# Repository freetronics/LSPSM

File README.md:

Freetronics LibreSat Power Supply Module
========================================
Copyright 2013 Freetronics Pty Ltd  
Freetronics site:  www.freetronics.com.au  
Freetronics email: info@freetronics.com.au  

FIXME

Features:

 * FIXME

More information is available at:

  http://www.freetronics.com.au/lspsm

INSTALLATION
------------
The design is saved as an EAGLE project. EAGLE PCB design software is
available from www.cadsoftusa.com free for non-commercial use. To use
this project download it and place the directory containing these files
into the "eagle" directory on your computer. Then open EAGLE and
navigate to the project.

DISTRIBUTION
------------
The specific terms of distribution of this project are governed by the
license referenced below.

LICENSE
-------
Licensed under the TAPR Open Hardware License (www.tapr.org/OHL).
The "license" folder within this repository also contains a copy of
this license in plain text format.

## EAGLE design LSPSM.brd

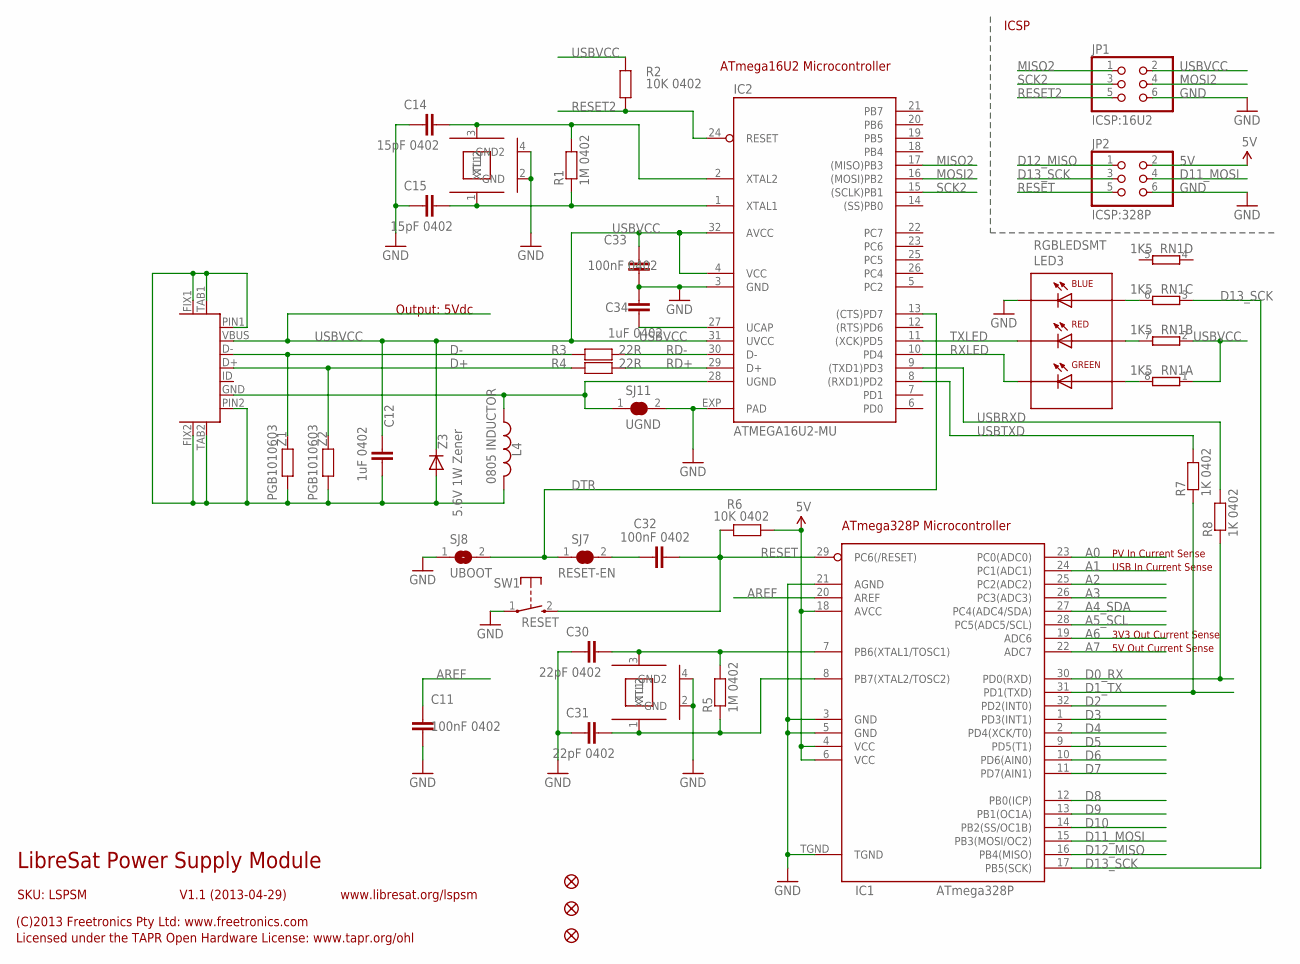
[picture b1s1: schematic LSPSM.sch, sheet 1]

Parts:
C11, C32, C33: 100nF 0402; 0402C
C12, C34: 1uF 0402; 0402C
C14, C15: 15pF 0402; 0402C
C30, C31: 22pF 0402; 0402C
FID1, FID2, FID3: FIDUCIAL1X2.5; FIDUCIAL-1X2.5
IC1: ATmega328P; MLF32
IC2: ATMEGA16U2-MU; ATMEL_QFN32
JP1: ICSP:16U2; 2X03
JP2: ICSP:328P; 2X03
L4: 0805 INDUCTOR; 0805-LARGE
LED3: RGBLEDSMT; 19-337
R1, R5: 1M 0402; 0402
R2, R6: 10K 0402; 0402
R3, R4: 22R; 0402
R7, R8: 1K 0402; 0402
RN1: 1K5; CAY16
S1: USB-6PSMT; USB-MICROB-MB05PMXX
SJ7: RESET-EN; 0402SJC
SJ8: UBOOT; 0402SJO
SJ11: UGND; 0402SJC
SW1: RESET; TACTILE_SWITCH_SMD_2PIN_TINY
XTL1, XTL2: 16MHz; CRYSTAL-SMD-3X2
Z1, Z2: PGB1010603; 0603
Z3: 5.6V 1W Zener; SMA-DIODE

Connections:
5V: IC1.4 (VCC), IC1.6 (VCC), IC1.18 (AVCC), JP2.2, R6.2; also elsewhere on the board
A0: IC1.23 (PC0(ADC0)); also elsewhere on the board
A1: IC1.24 (PC1(ADC1)); also elsewhere on the board
A2: IC1.25 (PC2(ADC2)); also elsewhere on the board
A3: IC1.26 (PC3(ADC3)); also elsewhere on the board
A4_SDA: IC1.27 (PC4(ADC4/SDA)); also elsewhere on the board
A5_SCL: IC1.28 (PC5(ADC5/SCL)); also elsewhere on the board
A6: IC1.19 (ADC6); also elsewhere on the board
A7: IC1.22 (ADC7); also elsewhere on the board
AREF: C11.1, IC1.20 (AREF); also elsewhere on the board
D0_RX: IC1.30 (PD0(RXD)), R8.1; also elsewhere on the board
D1_TX: IC1.31 (PD1(TXD)), R7.1; also elsewhere on the board
D2: IC1.32 (PD2(INT0)); also elsewhere on the board
D3: IC1.1 (PD3(INT1)); also elsewhere on the board
D4: IC1.2 (PD4(XCK/T0)); also elsewhere on the board
D5: IC1.9 (PD5(T1)); also elsewhere on the board
D6: IC1.10 (PD6(AIN0)); also elsewhere on the board
D7: IC1.11 (PD7(AIN1)); also elsewhere on the board
D8: IC1.12 (PB0(ICP)); also elsewhere on the board
D9: IC1.13 (PB1(OC1A)); also elsewhere on the board
D10: IC1.14 (PB2(SS/OC1B)); also elsewhere on the board
D11_MOSI: IC1.15 (PB3(MOSI/OC2)), JP2.4; also elsewhere on the board
D12_MISO: IC1.16 (PB4(MISO)), JP2.1; also elsewhere on the board
D13_SCK: IC1.17 (PB5(SCK)), JP2.3, RN1.3 (1); also elsewhere on the board
D+: R4.1, S1.D+, Z2.2
D-: R3.1, S1.D-, Z1.2
DTR: IC2.13 ((CTS)PD7), SJ7.1, SJ8.2
GND: C11.2, C14.1, C15.1, C30.1, C31.1, C33.2, C34.2, IC1.3 (GND), IC1.5 (GND), IC1.21 (AGND), IC1.TGND, IC2.3 (GND), IC2.EXP (PAD), JP1.6, JP2.6, LED3.1 (C-B), SJ8.1, SJ11.2, SW1.1, XTL1.2 (GND), XTL1.4 (GND2), XTL2.2 (GND), XTL2.4 (GND2); also elsewhere on the board
MISO2: IC2.17 ((MISO)PB3), JP1.1
MOSI2: IC2.16 ((MOSI)PB2), JP1.4
unnamed: C30.2, IC1.7 (PB6(XTAL1/TOSC1)), R5.2, XTL2.3 (XTL2)
unnamed: C15.2, IC2.1 (XTAL1), R1.1, XTL1.1 (XTL1)
unnamed: LED3.4 (A-B), RN1.6 (2)
unnamed: LED3.5 (A-R), RN1.7 (2)
unnamed: LED3.6 (A-G), RN1.8 (2)
unnamed: C31.2, IC1.8 (PB7(XTAL2/TOSC2)), R5.1, XTL2.1 (XTL1)
unnamed: C34.1, IC2.27 (UCAP)
unnamed: C12.2, L4.2, S1.FIX1, S1.FIX2, S1.PIN1, S1.PIN2, S1.TAB1, S1.TAB2, Z1.1, Z2.1, Z3.A
unnamed: C14.2, IC2.2 (XTAL2), R1.2, XTL1.3 (XTL2)
unnamed: IC2.28 (UGND), L4.1, S1.GND, SJ11.1
unnamed: C32.1, SJ7.2
RD+: IC2.29 (D+), R4.2
RD-: IC2.30 (D-), R3.2
RESET: C32.2, IC1.29 (PC6(/RESET)), JP2.5, R6.1, SW1.2 (S); also elsewhere on the board
RESET2: IC2.24 (RESET), JP1.5, R2.1
RXLED: IC2.10 (PD4), LED3.3 (C-G)
SCK2: IC2.15 ((SCLK)PB1), JP1.3
TXLED: IC2.11 ((XCK)PD5), LED3.2 (C-R)
USBRXD: IC2.9 ((TXD1)PD3), R8.2
USBTXD: IC2.8 ((RXD1)PD2), R7.2
USBVCC: C12.1, C33.1, IC2.4 (VCC), IC2.31 (UVCC), IC2.32 (AVCC), JP1.2, R2.2, RN1.1, RN1.2 (1), S1.VBUS, Z3.C; also elsewhere on the board

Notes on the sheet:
ATmega328P Microcontroller
ATmega16U2 Microcontroller
PV In Current Sense
5V Out Current Sense
3V3 Out Current Sense
USB In Current Sense
Output: 5Vdc
LibreSat Power Supply Module
V1.1 (2013-04-29)
SKU: LSPSM
(C)2013 Freetronics Pty Ltd: www.freetronics.com
Licensed under the TAPR Open Hardware License: www.tapr.org/ohl
www.libresat.org/lspsm
ICSP

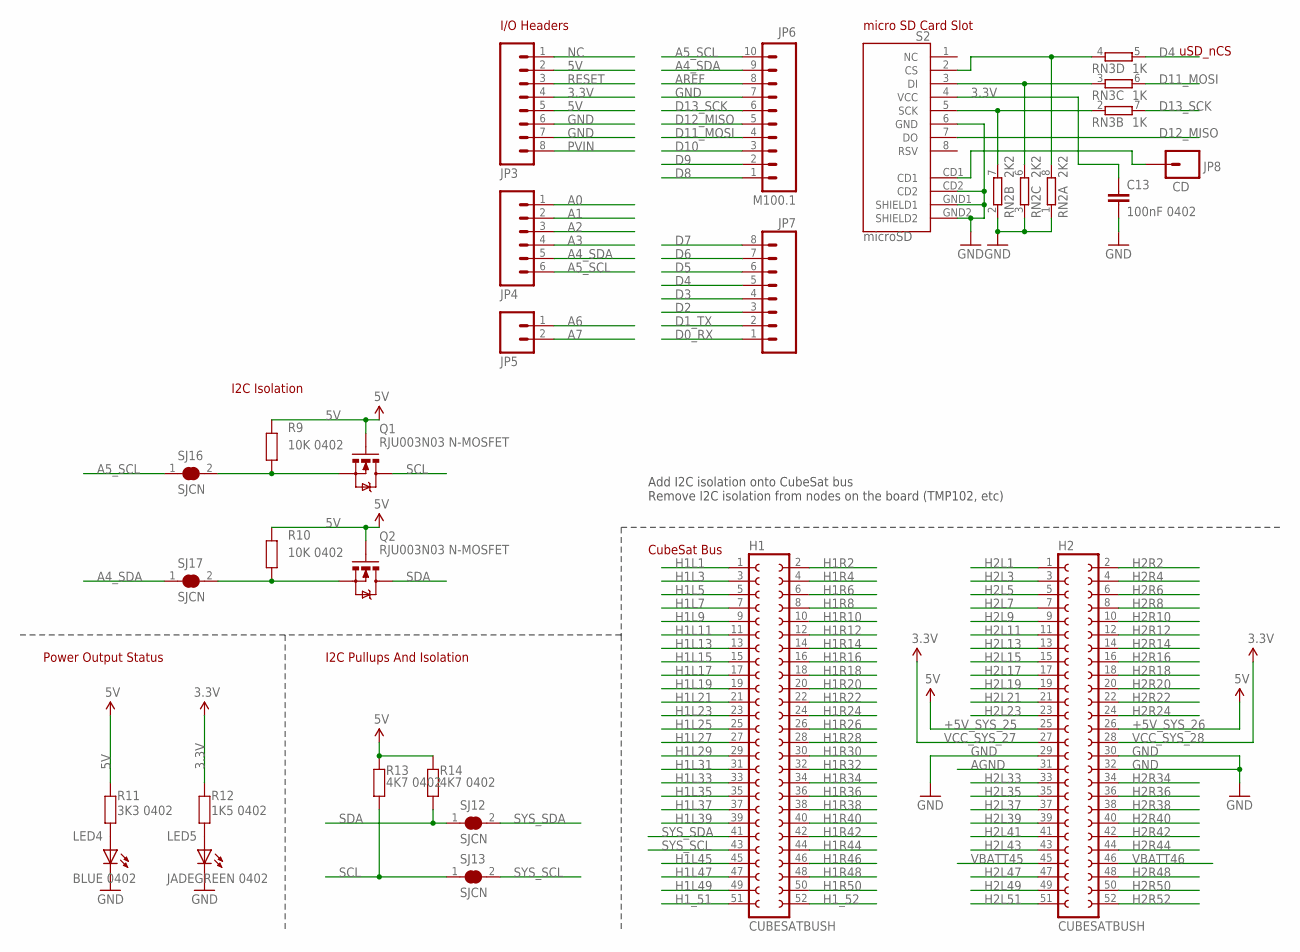
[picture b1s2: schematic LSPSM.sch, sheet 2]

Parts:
C13: 100nF 0402; 0402C
H1, H2: CUBESATBUSH; CUBESATBUS
JP3, JP7: M08; 1X08
JP4: M06SIP; 1X06
JP5: M02PTH; 1X02
JP6: M100.1; 1X10
JP8: CD; 1X01
LED4: BLUE 0402; LED-0402
LED5: JADEGREEN 0402; LED-0402
Q1, Q2: RJU003N03 N-MOSFET; SOT32-3
R9, R10: 10K 0402; 0402
R11: 3K3 0402; 0402
R12: 1K5 0402; 0402
R13, R14: 4K7 0402; 0402
RN2: 2K2; CAY16
RN3: 1K; CAY16
S2: microSD; MICRO-SD-SOCKET-PP
SJ12, SJ13, SJ16, SJ17: SJCN; SJC

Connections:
3.3V: C13.1, JP3.4, R12.1, S2.4 (VCC); also elsewhere on the board
5V: JP3.2, JP3.5, Q1.1 (G), Q2.1 (G), R9.2, R10.2, R11.1, R13.2, R14.2; also elsewhere on the board
+5V_SYS_25: H2.25; also elsewhere on the board
+5V_SYS_26: H2.26; also elsewhere on the board
A0: JP4.1; also elsewhere on the board
A1: JP4.2; also elsewhere on the board
A2: JP4.3; also elsewhere on the board
A3: JP4.4; also elsewhere on the board
A4_SDA: JP4.5, JP6.9, SJ17.1; also elsewhere on the board
A5_SCL: JP4.6, JP6.10, SJ16.1; also elsewhere on the board
A6: JP5.1; also elsewhere on the board
A7: JP5.2; also elsewhere on the board
AGND: H2.31
AREF: JP6.8; also elsewhere on the board
D0_RX: JP7.1; also elsewhere on the board
D1_TX: JP7.2; also elsewhere on the board
D2: JP7.3; also elsewhere on the board
D3: JP7.4; also elsewhere on the board
D4: JP7.5, RN3.5 (2); also elsewhere on the board
D5: JP7.6; also elsewhere on the board
D6: JP7.7; also elsewhere on the board
D7: JP7.8; also elsewhere on the board
D8: JP6.1; also elsewhere on the board
D9: JP6.2; also elsewhere on the board
D10: JP6.3; also elsewhere on the board
D11_MOSI: JP6.4, RN3.6 (2); also elsewhere on the board
D12_MISO: JP6.5, S2.7 (DO); also elsewhere on the board
D13_SCK: JP6.6, RN3.7 (2); also elsewhere on the board
GND: C13.2, H2.29, H2.30, H2.32, JP3.6, JP3.7, JP6.7, LED4.C, LED5.C, RN2.1, RN2.2 (1), RN2.3 (1), S2.6 (GND), S2.CD2, S2.GND1 (SHIELD1), S2.GND2 (SHIELD2); also elsewhere on the board
H1L1: H1.1
H1L3: H1.3
H1L5: H1.5
H1L7: H1.7
H1L9: H1.9
H1L11: H1.11
H1L13: H1.13
H1L15: H1.15
H1L17: H1.17
H1L19: H1.19
H1L21: H1.21
H1L23: H1.23
H1L25: H1.25
H1L27: H1.27
H1L29: H1.29
H1L31: H1.31
H1L33: H1.33
H1L35: H1.35
H1L37: H1.37
H1L39: H1.39
H1L45: H1.45
H1L47: H1.47
H1L49: H1.49
H1R2: H1.2
H1R4: H1.4
H1R6: H1.6
H1R8: H1.8
H1R10: H1.10
H1R12: H1.12
H1R14: H1.14
H1R16: H1.16
H1R18: H1.18
H1R20: H1.20
H1R22: H1.22
H1R24: H1.24
H1R26: H1.26
H1R28: H1.28
H1R30: H1.30
H1R32: H1.32
H1R34: H1.34
H1R36: H1.36
H1R38: H1.38
H1R40: H1.40
H1R42: H1.42
H1R44: H1.44
H1R46: H1.46
H1R48: H1.48
H1R50: H1.50
H1_51: H1.51
H1_52: H1.52
H2L1: H2.1
H2L3: H2.3
H2L5: H2.5
H2L7: H2.7
H2L9: H2.9
H2L11: H2.11
H2L13: H2.13
H2L15: H2.15
H2L17: H2.17
H2L19: H2.19
H2L21: H2.21
H2L23: H2.23
H2L33: H2.33
H2L35: H2.35
H2L37: H2.37
H2L39: H2.39
H2L41: H2.41
H2L43: H2.43
H2L47: H2.47
H2L49: H2.49
H2L51: H2.51
H2R2: H2.2
H2R4: H2.4
H2R6: H2.6
H2R8: H2.8
H2R10: H2.10
H2R12: H2.12
H2R14: H2.14
H2R16: H2.16
H2R18: H2.18
H2R20: H2.20
H2R22: H2.22
H2R24: H2.24
H2R34: H2.34
H2R36: H2.36
H2R38: H2.38
H2R40: H2.40
H2R42: H2.42
H2R44: H2.44
H2R48: H2.48
H2R50: H2.50
H2R52: H2.52
unnamed: LED5.A, R12.2
unnamed: LED4.A, R11.2
unnamed: RN2.8 (2), RN3.4 (1), S2.2 (CS)
unnamed: RN2.6 (2), RN3.3 (1), S2.3 (DI)
unnamed: RN2.7 (2), RN3.2 (1), S2.5 (SCK)
unnamed: JP8.1, S2.CD1
unnamed: Q1.2 (S), R9.1, SJ16.2
unnamed: Q2.2 (S), R10.1, SJ17.2
NC: JP3.1
PVIN: JP3.8; also elsewhere on the board
RESET: JP3.3; also elsewhere on the board
SCL: Q1.3 (D), R13.1, SJ13.1; also elsewhere on the board
SDA: Q2.3 (D), R14.1, SJ12.1; also elsewhere on the board
SYS_SCL: H1.43, SJ13.2
SYS_SDA: H1.41, SJ12.2
VBATT45: H2.45; also elsewhere on the board
VBATT46: H2.46; also elsewhere on the board
VCC_SYS_27: H2.27; also elsewhere on the board
VCC_SYS_28: H2.28; also elsewhere on the board

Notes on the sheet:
CubeSat Bus
Power Output Status
I2C Pullups And Isolation
uSD_nCS
micro SD Card Slot
I2C Isolation
I/O Headers
Add I2C isolation onto CubeSat bus Remove I2C isolation from nodes on the board (TMP102, etc)

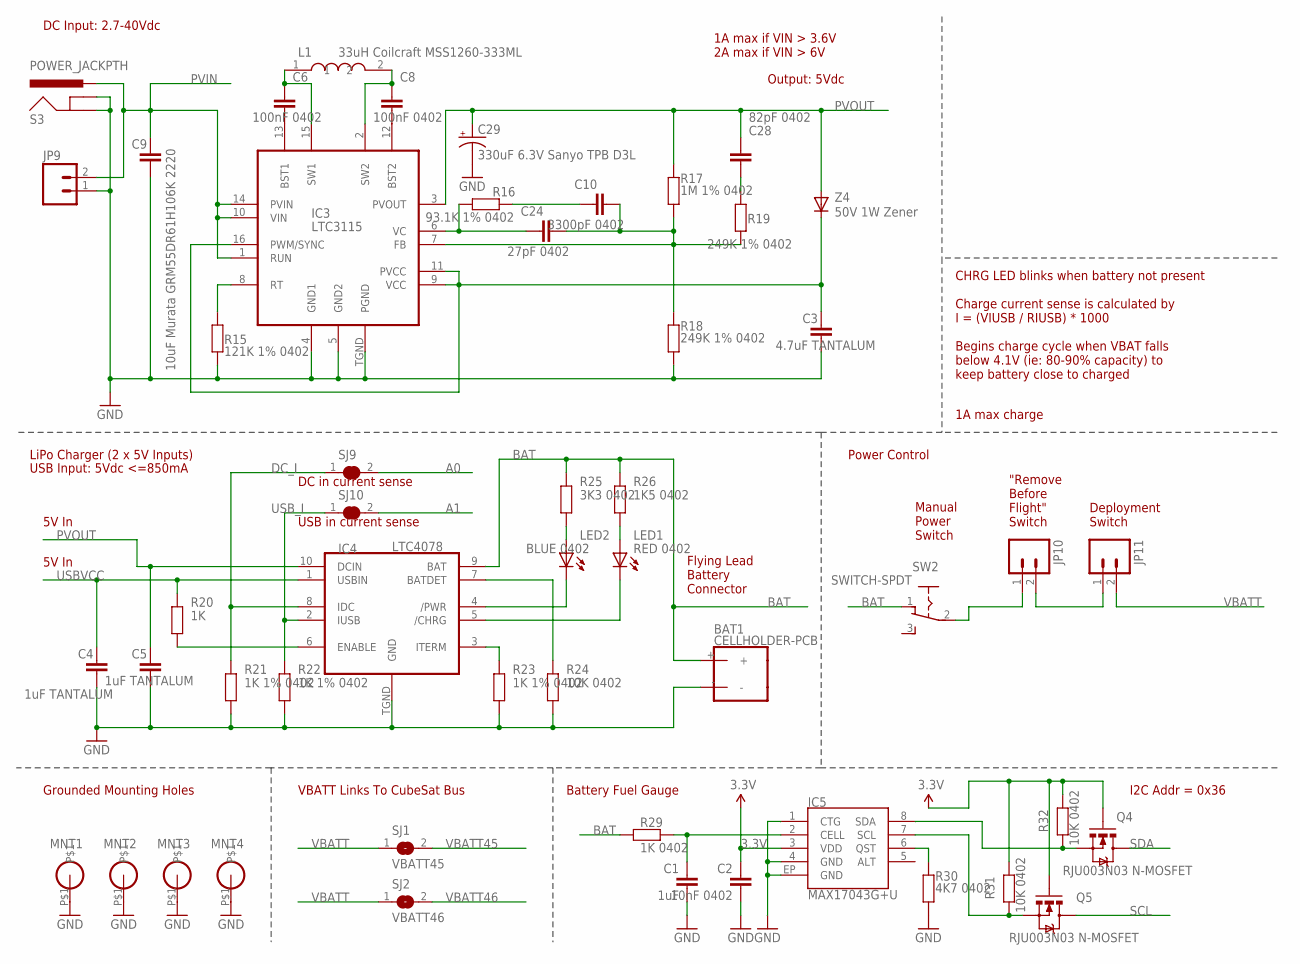
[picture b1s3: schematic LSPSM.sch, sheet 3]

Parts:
BAT1: CELLHOLDER-PCB; BH-18650-PC
C1: 1uF; 0402C
C2: 10nF 0402; 0402C
C3: 4.7uF TANTALUM; C1206K
C4, C5: 1uF TANTALUM; C1206K
C6, C8: 100nF 0402; 0402C
C9: 10uF Murata GRM55DR61H106K 2220; C2220K
C10: 3300pF 0402; 0402C
C24: 27pF 0402; 0402C
C28: 82pF 0402; 0402C
C29: 330uF 6.3V Sanyo TPB D3L; D3L
IC3: LTC3115; DFN-16
IC4: LTC4078; DFN-10
IC5: MAX17043G+U; TDFN-8
JP9, JP10, JP11: M02PTH; 1X02
L1: 33uH Coilcraft MSS1260-333ML; MSS1260
LED1: RED 0402; LED-0402
LED2: BLUE 0402; LED-0402
MNT1, MNT2, MNT3, MNT4: HOLE3.2MM; HOLE32
Q4, Q5: RJU003N03 N-MOSFET; SOT32-3
R15: 121K 1% 0402; 0402
R16: 93.1K 1% 0402; 0402
R17: 1M 1% 0402; 0402
R18, R19: 249K 1% 0402; 0402
R20: 1K; 0402
R21, R22, R23: 1K 1% 0402; 0402
R24, R31, R32: 10K 0402; 0402
R25: 3K3 0402; 0402
R26: 1K5 0402; 0402
R29: 1K 0402; 0402
R30: 4K7 0402; 0402
S3: POWER_JACKPTH; POWER_JACK_PTH
SJ1: VBATT45; SJ
SJ2: VBATT46; SJ
SJ9: DC_I; SJC
SJ10: USB_I; SJC
SW2: SWITCH-SPDT; SS-12F100
Z4: 50V 1W Zener; SMA-DIODE

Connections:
3.3V: C2.1, IC5.3 (VDD), Q4.1 (G), Q5.1 (G), R31.2, R32.2; also elsewhere on the board
A0: SJ9.2; also elsewhere on the board
A1: SJ10.2; also elsewhere on the board
BAT: BAT1.+, IC4.9 (BAT), R25.1, R26.1, R29.2, SW2.1
CELL: C1.1, IC5.2 (CELL), R29.1
DC_I: IC4.8 (IDC), R21.1, SJ9.1
GND: BAT1.-, C1.2, C2.2, C3.1, C4.1, C5.1, C9.1, C29.NEG (-), IC3.4 (GND1), IC3.5 (GND2), IC3.TGND (PGND), IC4.TGND (GND), IC5.1 (CTG), IC5.4 (GND), IC5.EP (GND), JP9.1, MNT1.P$1, MNT2.P$1, MNT3.P$1, MNT4.P$1, R15.1, R18.1, R21.2, R22.2, R23.2, R24.2, R30.1, S3.GND, S3.GNDBREAK; also elsewhere on the board
unnamed: JP10.2, JP11.1
unnamed: LED2.A, R25.2
unnamed: JP10.1, SW2.2
unnamed: IC5.8 (SDA), Q4.2 (S), R32.1
unnamed: IC5.7 (SCL), Q5.2 (S), R31.1
unnamed: IC4.7 (BATDET), R24.1
unnamed: IC4.4 (/PWR), LED2.C
unnamed: IC4.3 (ITERM), R23.1
unnamed: IC4.6 (ENABLE), R20.2
unnamed: C10.1, R16.2
unnamed: C3.2, IC3.9 (VCC), IC3.11 (PVCC), IC3.16 (PWM/SYNC), Z4.C
unnamed: C6.2, IC3.13 (BST1)
unnamed: C8.2, IC3.12 (BST2)
unnamed: C6.1, IC3.15 (SW1), L1.1
unnamed: C8.1, IC3.2 (SW2), L1.2
unnamed: C24.1, IC3.6 (VC), R16.1
unnamed: C10.2, C24.2, IC3.7 (FB), R17.1, R18.2, R19.1
unnamed: IC3.8 (RT), R15.2
unnamed: C28.2, R19.2
unnamed: LED1.A, R26.2
unnamed: IC4.5 (/CHRG), LED1.C
PVIN: C9.2, IC3.1 (RUN), IC3.10 (VIN), IC3.14 (PVIN), JP9.2, S3.PWR; also elsewhere on the board
PVOUT: C5.2, C28.1, C29.POS (+), IC3.3 (PVOUT), IC4.10 (DCIN), R17.2, Z4.A
QST: IC5.6 (QST), R30.2
SCL: Q5.3 (D); also elsewhere on the board
SDA: Q4.3 (D); also elsewhere on the board
USBVCC: C4.2, IC4.1 (USBIN), R20.1; also elsewhere on the board
USB_I: IC4.2 (IUSB), R22.1, SJ10.1
VBATT: JP11.2, SJ1.1, SJ2.1; also elsewhere on the board
VBATT45: SJ1.2; also elsewhere on the board
VBATT46: SJ2.2; also elsewhere on the board

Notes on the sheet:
LiPo Charger (2 x 5V Inputs)
I2C Addr = 0x36
"Remove Before Flight" Switch
Deployment Switch
Manual Power Switch
Flying Lead Battery Connector
CHRG LED blinks when battery not present Charge current sense is calculated by I = (VIUSB / RIUSB) * 1000 Begins charge cycle when VBAT falls below 4.1V (ie: 80-90% capacity) to keep battery close to charged
1A max charge
DC in current sense
USB in current sense
1A max if VIN > 3.6V 2A max if VIN > 6V
DC Input: 2.7-40Vdc
Grounded Mounting Holes
VBATT Links To CubeSat Bus
Battery Fuel Gauge
Power Control
Output: 5Vdc
5V In
USB Input: 5Vdc <=850mA

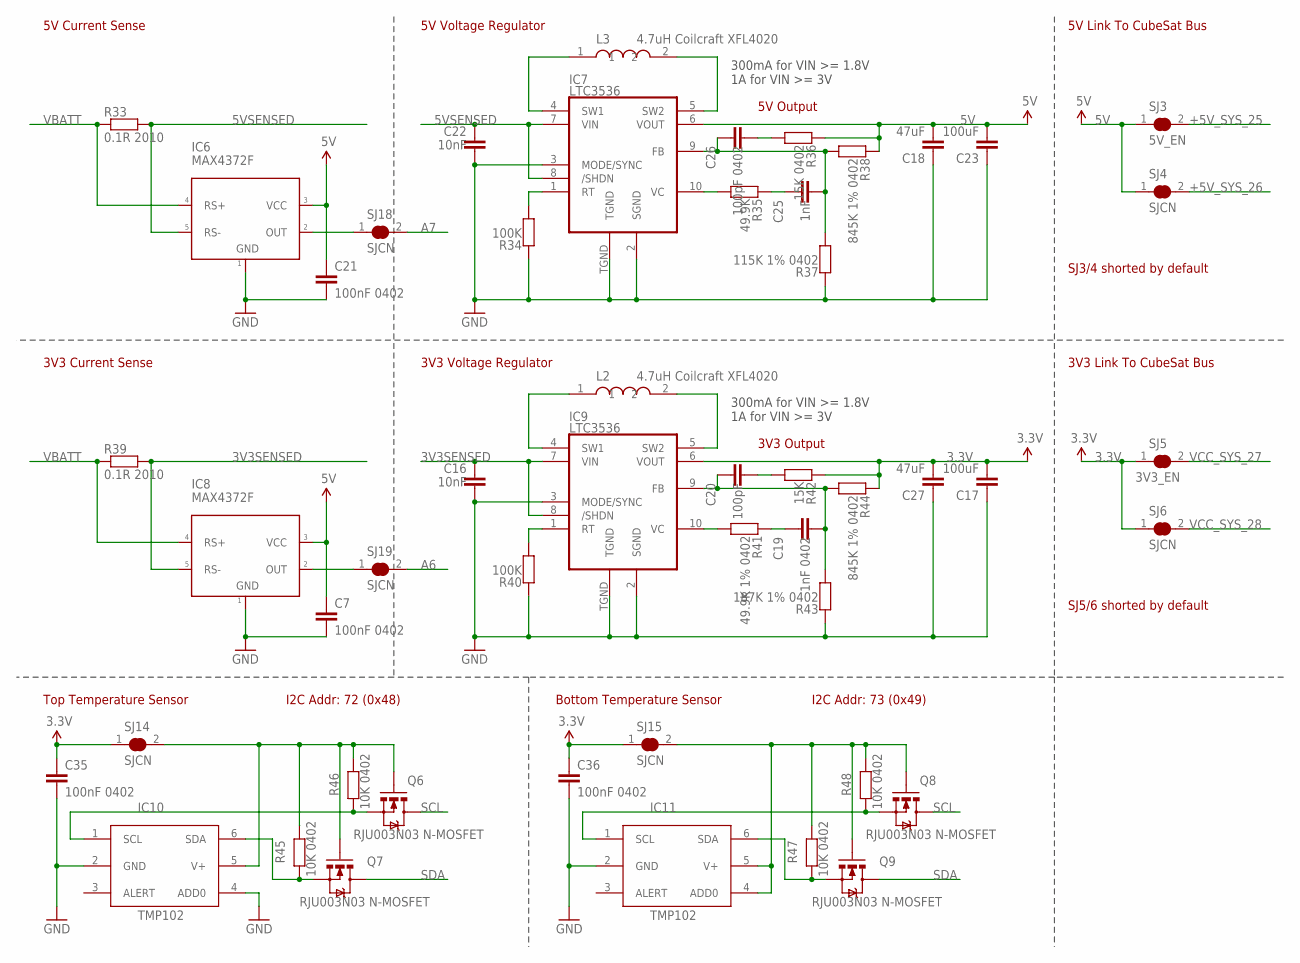
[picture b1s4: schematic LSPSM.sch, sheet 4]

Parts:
C7, C21, C35, C36: 100nF 0402; 0402C
C16, C22: 10nF; 0402C
C17, C23: 100uF; C1206K
C18, C27: 47uF; C1206K
C19: 1nF 0402; 0402C
C20: 100pF; 0402C
C25: 1nF; 0402C
C26: 100pF 0402; 0402C
IC6, IC8: MAX4372F; SOT23-5
IC7, IC9: LTC3536; DFN-10
IC10, IC11: TMP102; SOT563
L2, L3: 4.7uH Coilcraft XFL4020; XFL4020
Q6, Q7, Q8, Q9: RJU003N03 N-MOSFET; SOT32-3
R33, R39: 0.1R 2010; R2010
R34, R40: 100K; 0402
R35: 49.9K; 0402
R36: 15K 0402; 0402
R37: 115K 1% 0402; 0402
R38, R44: 845K 1% 0402; 0402
R41: 49.9K 1% 0402; 0402
R42: 15K; 0402
R43: 187K 1% 0402; 0402
R45, R46, R47, R48: 10K 0402; 0402
SJ3: 5V_EN; SJC
SJ4, SJ6, SJ14, SJ15, SJ18, SJ19: SJCN; SJC
SJ5: 3V3_EN; SJC

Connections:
3.3V: C17.2, C27.2, C35.1, C36.1, IC9.6 (VOUT), R42.2, R44.2, SJ5.1, SJ6.1, SJ14.1, SJ15.1; also elsewhere on the board
3V3SENSED: C16.1, IC8.5 (RS-), IC9.7 (VIN), IC9.8 (/SHDN), R39.2
5V: C7.1, C18.2, C21.1, C23.2, IC6.3 (VCC), IC7.6 (VOUT), IC8.3 (VCC), R36.2, R38.2, SJ3.1, SJ4.1; also elsewhere on the board
5VSENSED: C22.1, IC6.5 (RS-), IC7.7 (VIN), IC7.8 (/SHDN), R33.2
+5V_SYS_25: SJ3.2; also elsewhere on the board
+5V_SYS_26: SJ4.2; also elsewhere on the board
A6: SJ19.2; also elsewhere on the board
A7: SJ18.2; also elsewhere on the board
GND: C7.2, C16.2, C17.1, C18.1, C21.2, C22.2, C23.1, C27.1, C35.2, C36.2, IC6.1 (GND), IC7.2 (SGND), IC7.3 (MODE/SYNC), IC7.TGND, IC8.1 (GND), IC9.2 (SGND), IC9.3 (MODE/SYNC), IC9.TGND, IC10.2 (GND), IC10.4 (ADD0), IC11.2 (GND), R34.2, R37.2, R40.2, R43.2; also elsewhere on the board
unnamed: IC6.2 (OUT), SJ18.1
unnamed: IC9.10 (VC), R41.1
unnamed: IC9.4 (SW1), L2.1
unnamed: IC9.5 (SW2), L2.2
unnamed: IC9.1 (RT), R40.1
unnamed: IC7.4 (SW1), L3.1
unnamed: C19.1, R41.2
unnamed: C20.2, R42.1
unnamed: C19.2, C20.1, IC9.9 (FB), R43.1, R44.1
unnamed: IC7.5 (SW2), L3.2
unnamed: IC7.1 (RT), R34.1
unnamed: C25.1, R35.2
unnamed: IC7.10 (VC), R35.1
unnamed: C26.2, R36.1
unnamed: C25.2, C26.1, IC7.9 (FB), R37.1, R38.1
unnamed: IC8.2 (OUT), SJ19.1
unnamed: IC10.5 (V+), Q6.1 (G), Q7.1 (G), R45.2, R46.2, SJ14.2
unnamed: IC11.4 (ADD0), IC11.5 (V+), Q8.1 (G), Q9.1 (G), R47.2, R48.2, SJ15.2
unnamed: IC10.1 (SCL), Q6.2 (S), R46.1
unnamed: IC10.6 (SDA), Q7.2 (S), R45.1
unnamed: IC11.6 (SDA), Q9.2 (S), R47.1
unnamed: IC11.1 (SCL), Q8.2 (S), R48.1
SCL: Q6.3 (D), Q8.3 (D); also elsewhere on the board
SDA: Q7.3 (D), Q9.3 (D); also elsewhere on the board
VBATT: IC6.4 (RS+), IC8.4 (RS+), R33.1, R39.1; also elsewhere on the board
VCC_SYS_27: SJ5.2; also elsewhere on the board
VCC_SYS_28: SJ6.2; also elsewhere on the board

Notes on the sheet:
5V Link To CubeSat Bus
3V3 Output
5V Output
5V Current Sense
300mA for VIN >= 1.8V 1A for VIN >= 3V
3V3 Link To CubeSat Bus
5V Voltage Regulator
3V3 Current Sense
3V3 Voltage Regulator
Top Temperature Sensor
I2C Addr: 72 (0x48)
Bottom Temperature Sensor
I2C Addr: 73 (0x49)
SJ3/4 shorted by default
SJ5/6 shorted by default

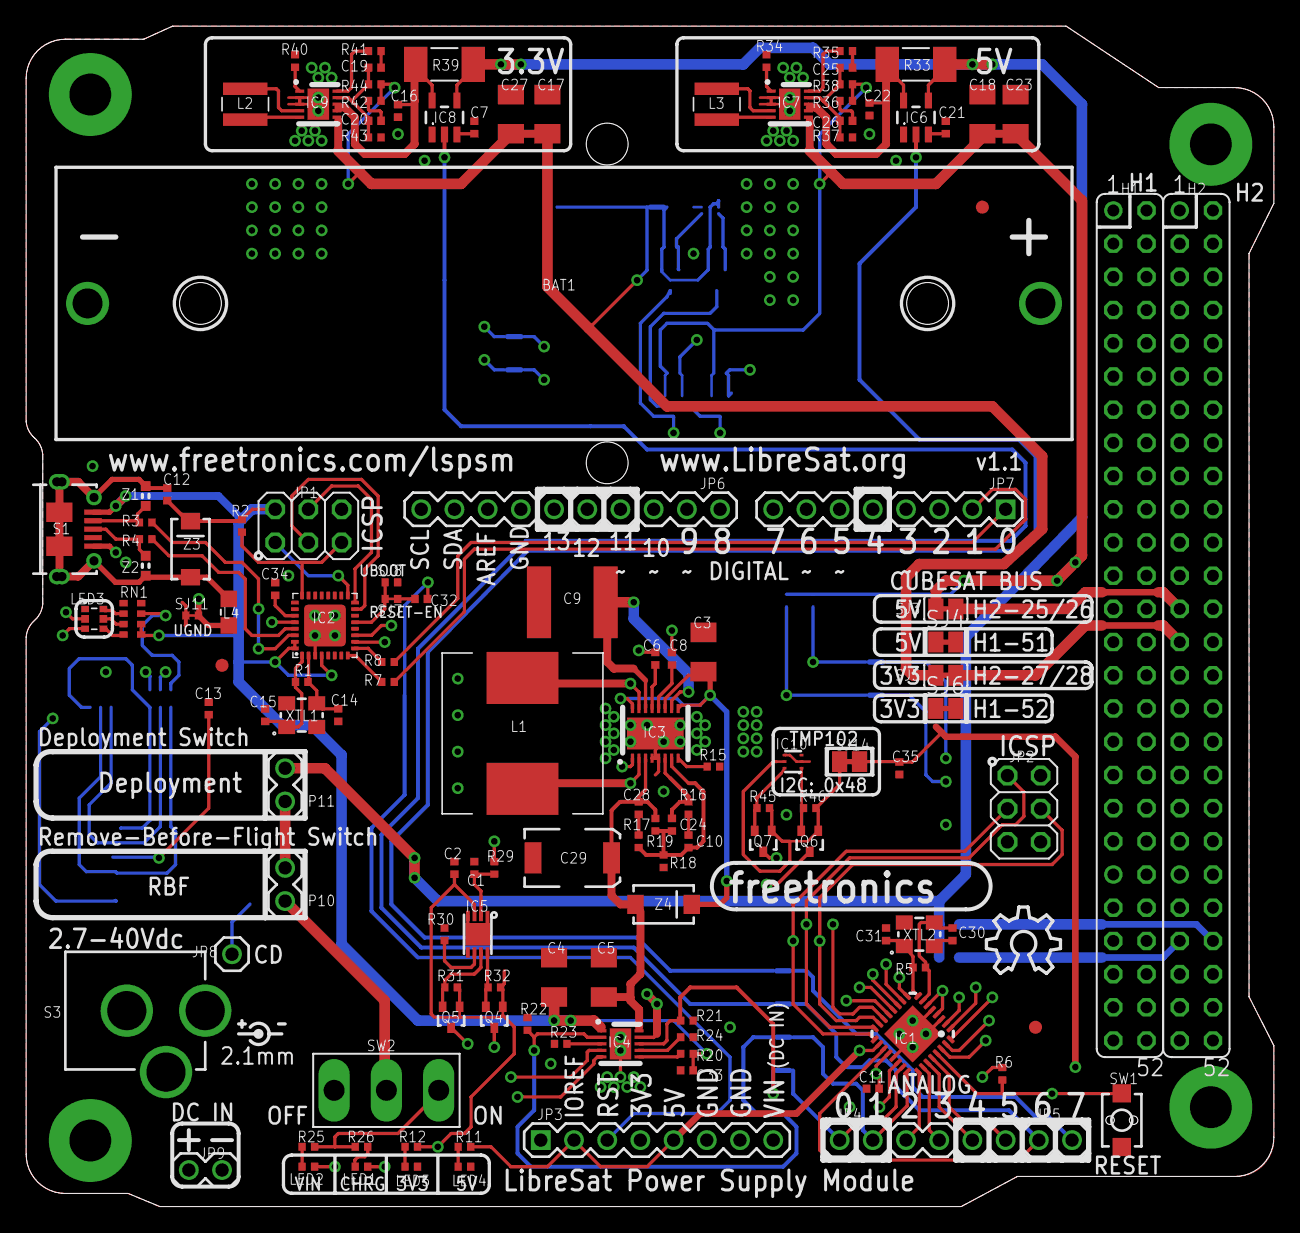
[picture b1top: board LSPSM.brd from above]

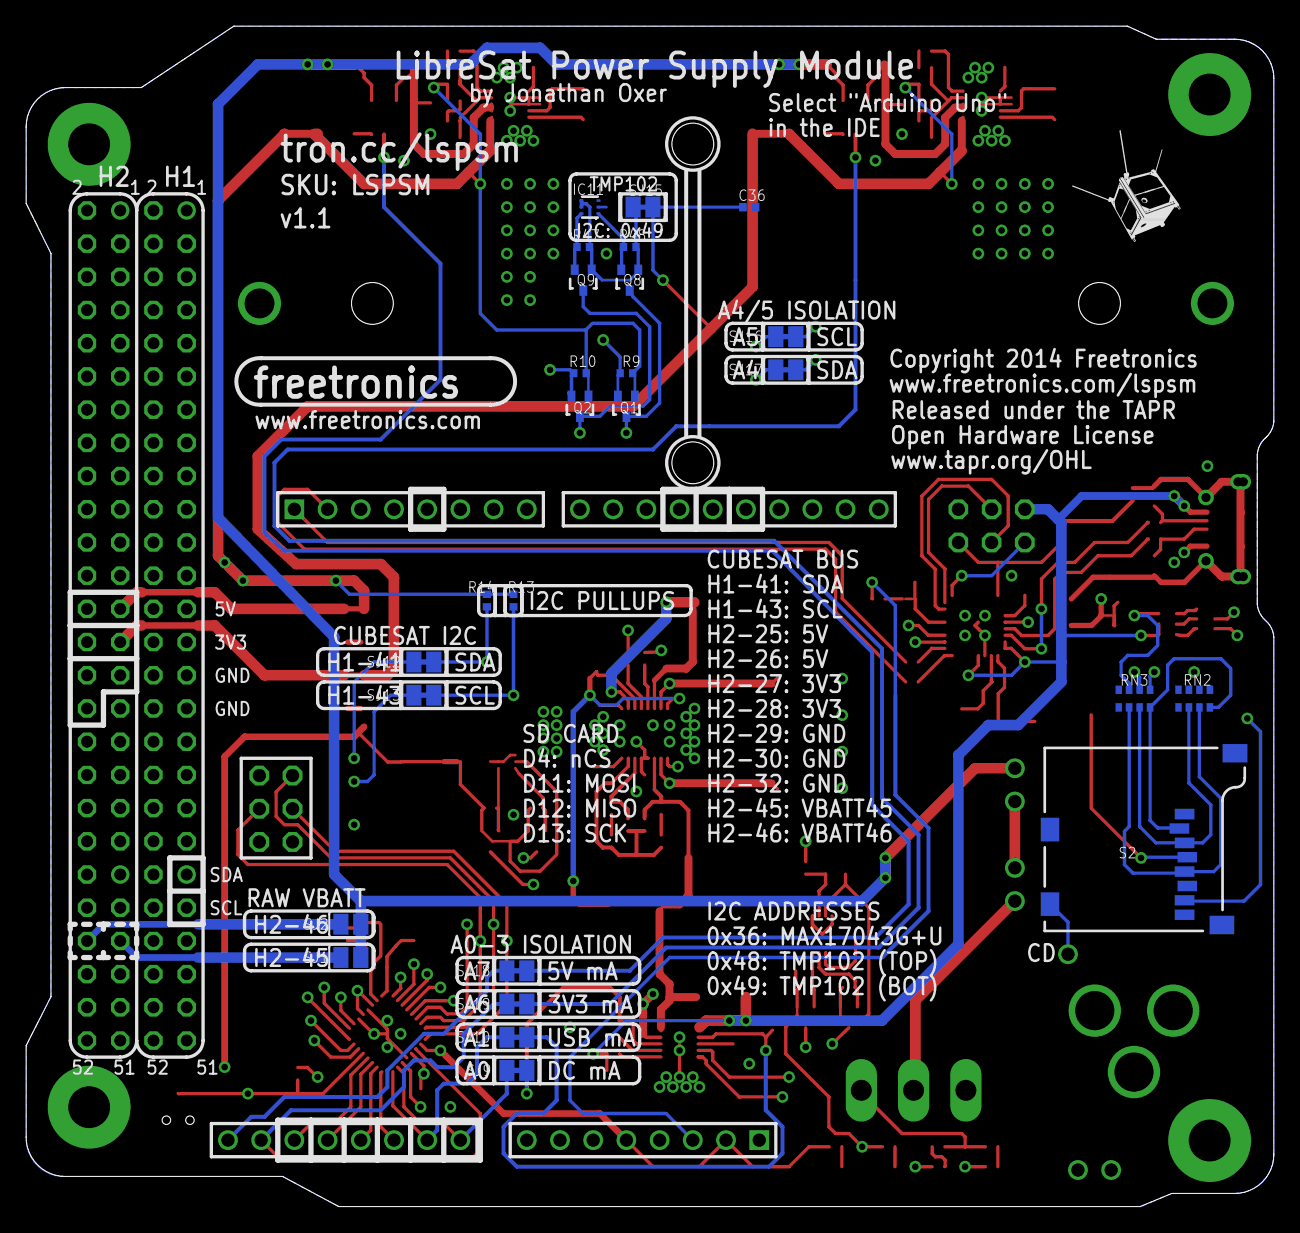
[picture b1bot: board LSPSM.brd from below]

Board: 4 copper layers, 95.5 x 90.3 mm, 165 parts (26 on the bottom side), 123 nets.

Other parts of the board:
U$2: OSHW_10X200_NOTEXT

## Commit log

2012-12-19 Initial project import
2012-12-19 Completed routing
2012-12-19 Updated Eagle project file
2012-12-20 Linked I2C with CubeSat bus; clearance and overlay improvements
2012-12-20 Added optional I2C pull-ups on CubeSat bus side of the isolators. Changed polygon isolation to 0.012 on inner layers, 0.010 on outer. Improved spacing.
2012-12-26 Added NanoSatisfi and ArduSat logos; clearances; DRC
2012-12-28 Moved 3.3V power supply input to before the 5V current sense resistor
2012-12-28 Via position change
2013-01-17 Routing, DRC, overlay
2013-04-24 Totally restructured project: single 18650 cell; 0402 parts; shield footprint; dual MCUs in Eleven architecture
2013-04-28 Routing done, clearances, DRC, overlay. Nearly ready for v1.0 release
2013-12-17 Changed max charge rate to 1A; removed solder jumpers for ArduSat power pins
2013-12-17 Changed current sense chip VCC to 5V
2017-08-24 Relabelled board from ArduSat to LibreSat
2017-08-24 Renamed board files from ArduSat to LibreSat
2017-08-24 Cleaned up old docs
2017-08-24 Removed ArduSat logo from silkscreen

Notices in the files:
LSPSM.brd:
Copyright 2014 Freetronics
parts and their libraries:
freetronics-original: Licensing: CC v3.0 Share-Alike You are welcome to use this library for commercial purposes.
